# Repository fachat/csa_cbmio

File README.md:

# CBM-IO

Note: this is a part of a larger set of repositories, with [upet_family](https://github.com/fachat/upet_family) as the main repository.

This is the IO board for a re-incarnation of the Commodore PET and B-Series to be used together with the Ultra-CPU board.

It is build on a Eurocard board and has only parts that can still be obtained new in 2025. In fact it uses an FPGA to emulate all the I/O chips of the PET or the B-Series.
It uses the [CS/A bus interface](http://www.6502.org/users/andre/csa/index.html) to connect with the CPU board.

The board at this time can only be programmed as I/O board for the PET, where it includes the original PET I/O (except the 2nd Tape), 
plus the extensions added in the [Ulti-PET](https://github.com/fachat/cbm_ultipet), namely the UART RS232 interfaces and the 2nd
VIA with the IEC bus interface. The VHDL code for this is found in the petio/ folder.

In the future there will be a second option to program the FPGA on the board for the I/O of the B-series.

Note: this is a work in progress!

## Features

## Contributions

### VIA 6522

The VIA6522 is coming from Rhialto's Mega65 code at https://github.com/Rhialto/MegaPET/blob/rhialto/CORE/PET2001_MiSTer/rtl/via6522.vhd
which in turns originates from Gideon Zweijtzer.

I had to adapt it to the single Phi2 clock input though.

In the meantime it has been mostly rewritten esp. in the timer and shift register parts, along the lines
of the chip dissection from http://forum.6502.org .

### UART 16550

The UART seems to be a common 16550 core, made for the Wishbone bus.
it is taken from the Microwatt project https://github.com/antonblanchard/microwatt
and seems to originate from http://www.opencores.org/cores/uart16550/ but that page is not found anymore.

I again had to adapt it to the 6502 bus interface.

## Thanks

Many thanks go to Frank "androSID" Wolf and Dieter "ttlworks" Müller from the
[6502.org forum](https://forum.6502.org), who dissected the PIA and VIA chips (and many more).
This is an outstanding work and absolutely helpful in understanding how the chips work internally.

The relevant chip dissections are

- [VIA dissection](https://6502.org/forum/viewtopic.php?f=4&t=7241)
- [PIA dissection](https://6502.org/forum/viewtopic.php?f=4&t=7425)

For your interest, the full list of chip dissection is here [here on the forum](https://6502.org/forum/viewtopic.php?t=7427)

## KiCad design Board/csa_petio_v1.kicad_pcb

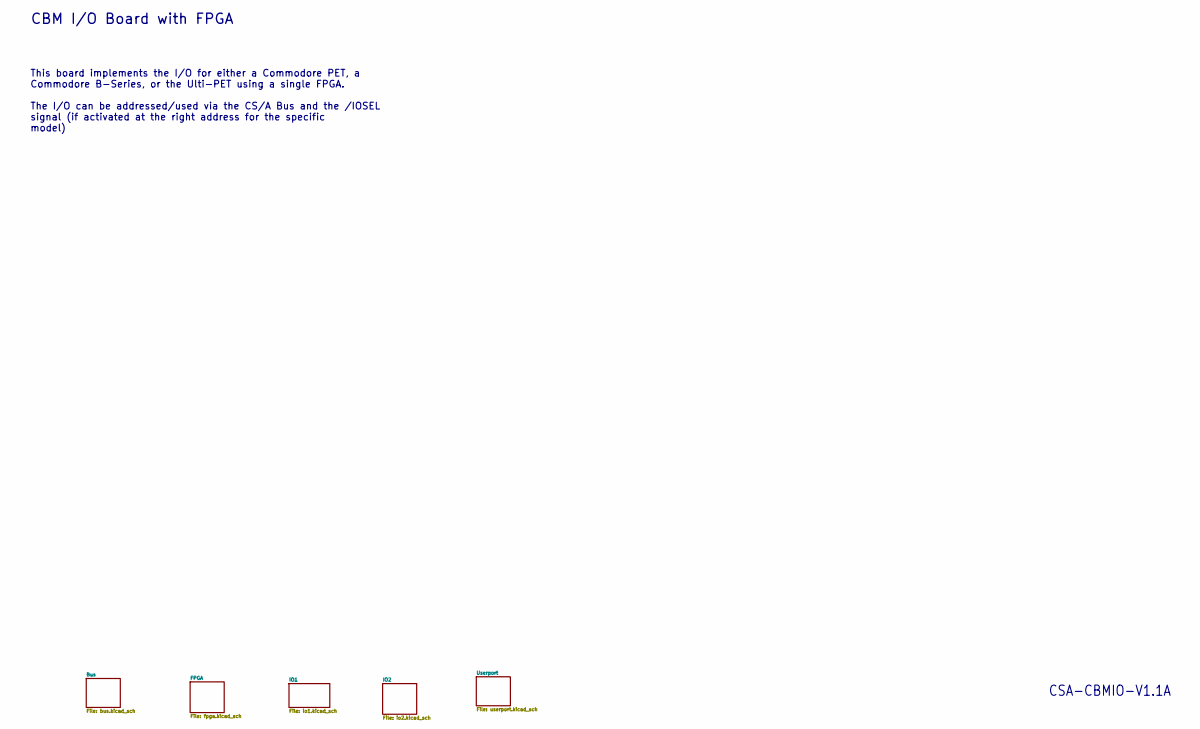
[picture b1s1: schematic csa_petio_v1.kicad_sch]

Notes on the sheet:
CBM I/O Board with FPGA
CSA-CBMIO-V1.1A
This board implements the I/O for either a Commodore PET, a Commodore B-Series, or the Ulti-PET using a single FPGA. The I/O can be addressed/used via the CS/A Bus and the /IOSEL signal (if activated at the right address for the specific model)

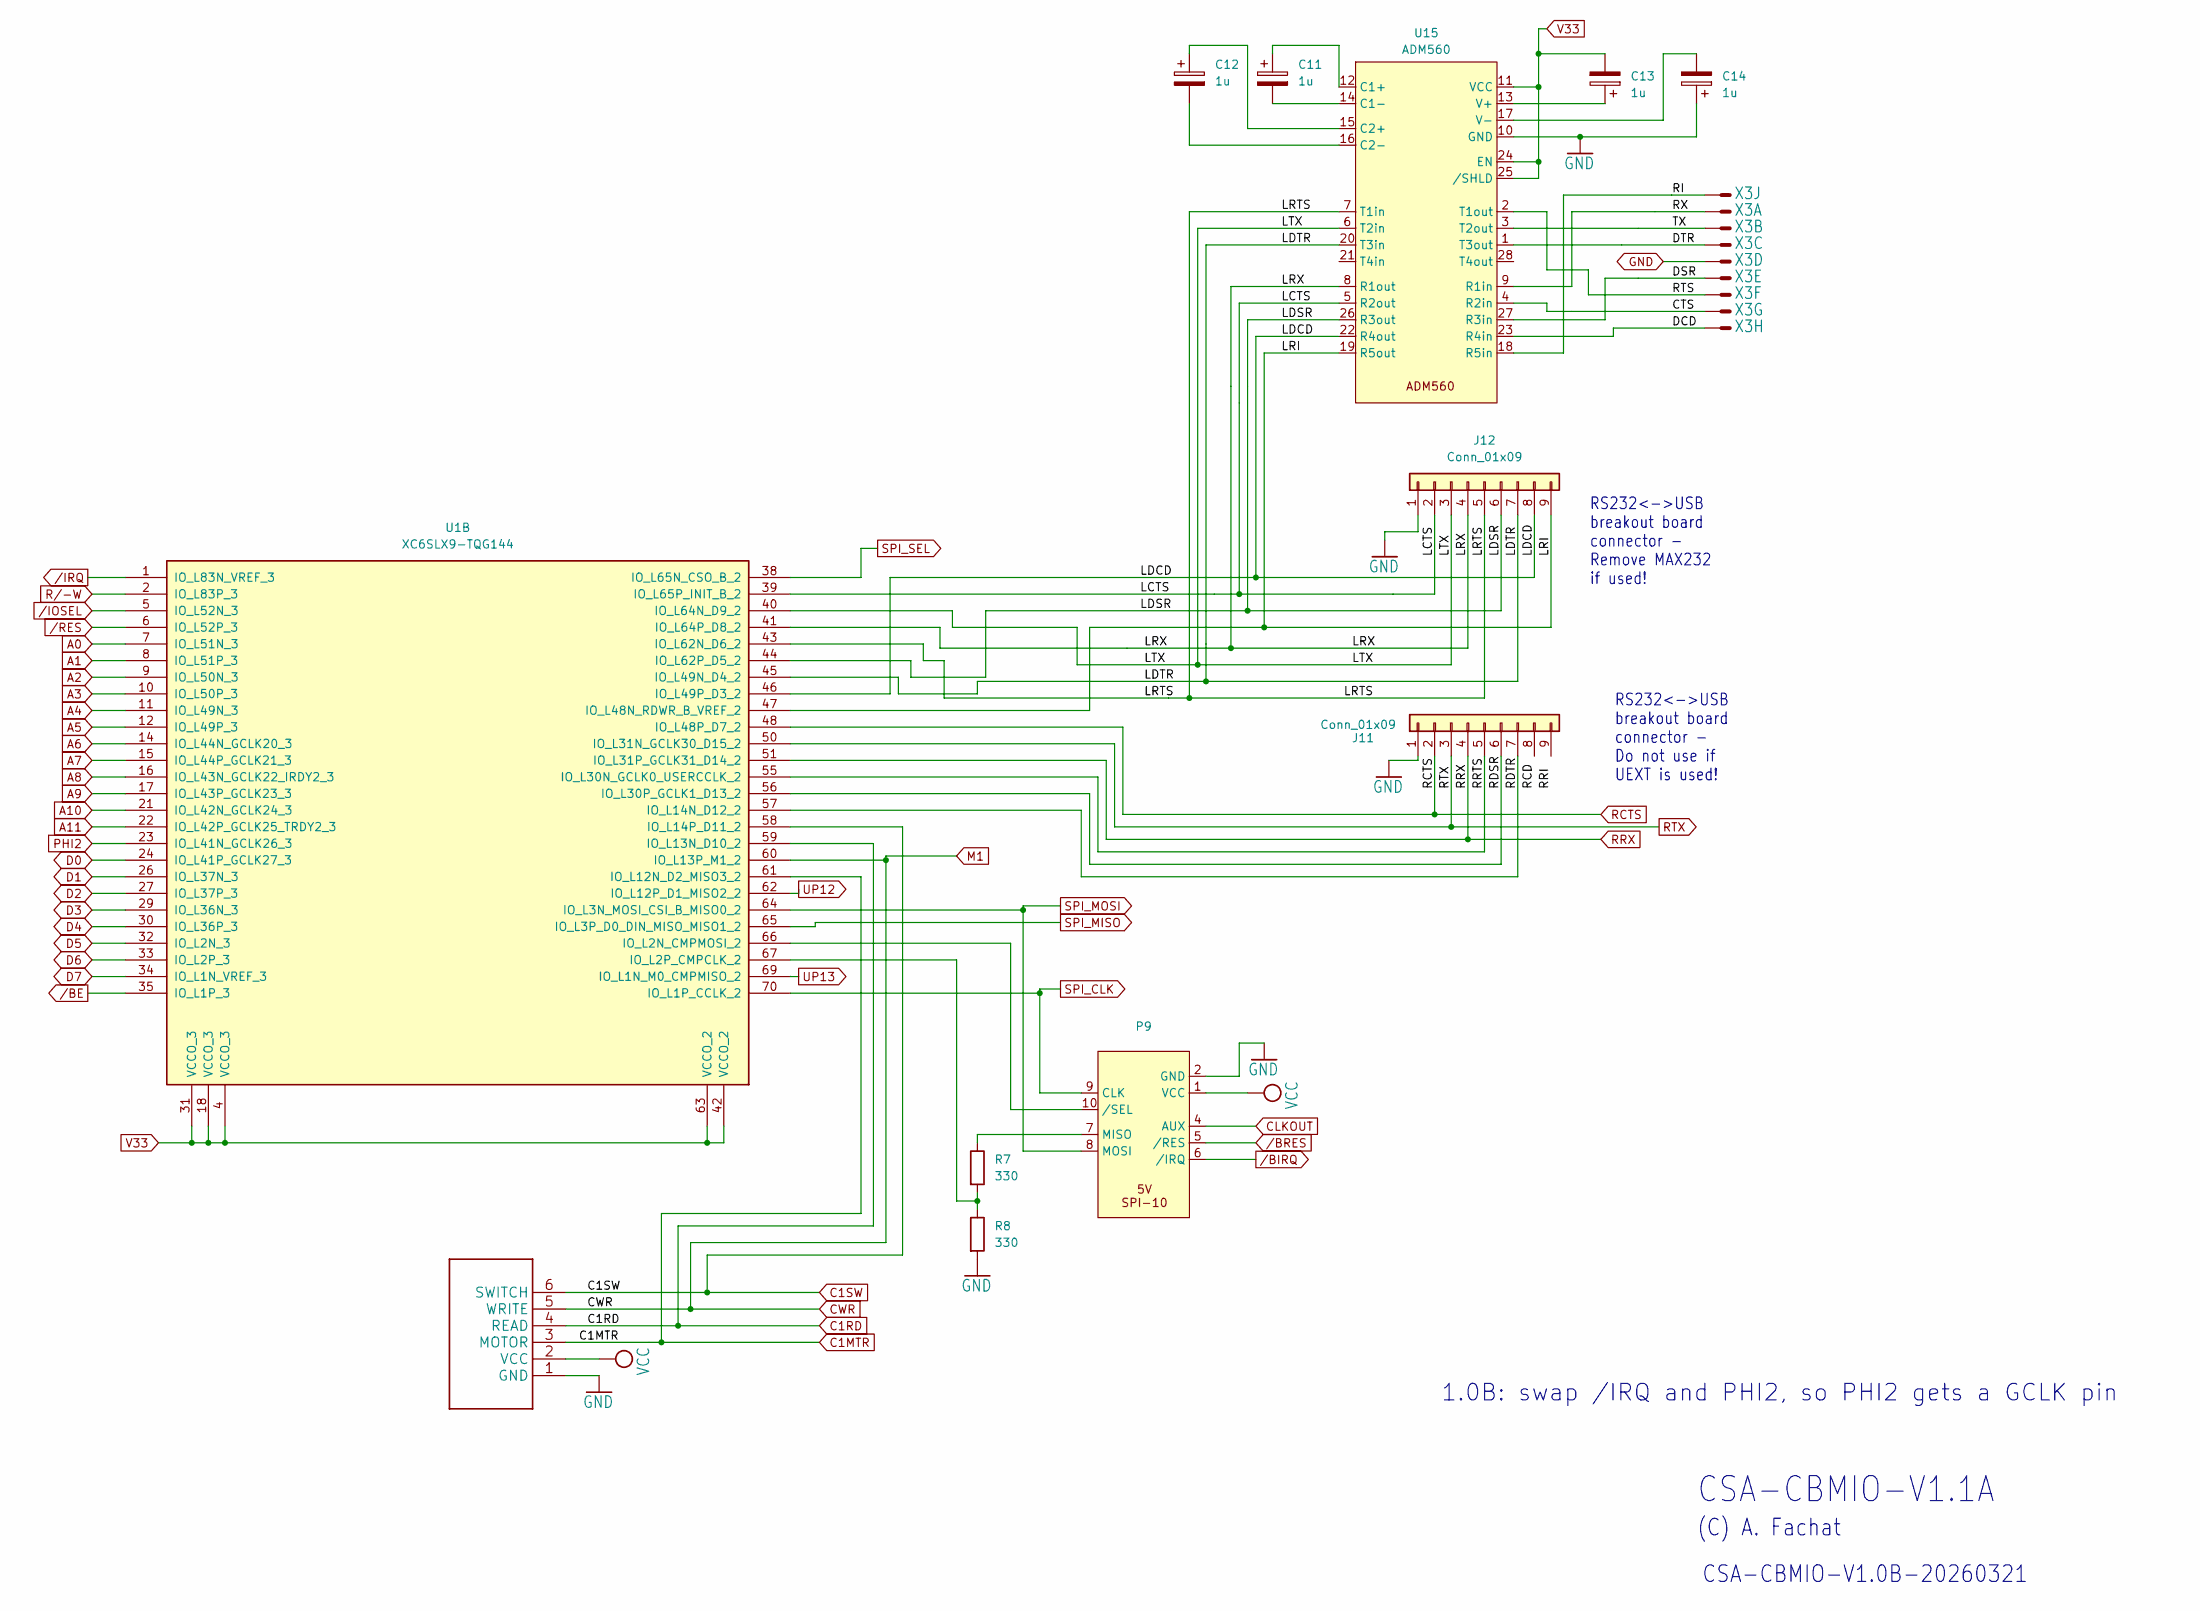
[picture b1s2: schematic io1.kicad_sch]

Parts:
C11, C12, C13, C14: 1u; C_0805_2012Metric_Pad1.18x1.45mm_HandSolder
J11, J12: Conn_01x09; PinHeader_1x09_P2.54mm_Vertical
P5: CBMTAPE; JP6
P9: IDC-Header_2x05_P2.54mm_Vertical
R7, R8: 330; R_0603_1608Metric_Pad0.98x0.95mm_HandSolder
U1: XC6SLX9-TQG144; TQFP-144_20x20mm_P0.5mm
U15: ADM560; SSOP-28_5.3x10.2mm_P0.65mm
X3: M09HPS; DSUB-9_Pins_Horizontal_P2.77x2.84mm_EdgePinOffset9.90mm_Hou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

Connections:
/IO1/CTS: U15.4 (R2in), X3.8 (M)
/IO1/DCD: U15.23 (R4in), X3.9 (M)
/IO1/DSR: U15.27 (R3in), X3.6 (M)
/IO1/DTR: U15.1 (T3out), X3.4 (M)
/IO1/LCTS: J12.2, U1.39 (IO_L65P_INIT_B_2), U15.5 (R2out)
/IO1/LDCD: J12.8, U1.46 (IO_L49P_D3_2), U15.22 (R4out)
/IO1/LDSR: J12.6, U1.44 (IO_L62P_D5_2), U15.26 (R3out)
/IO1/LDTR: J12.7, U1.45 (IO_L49N_D4_2), U15.20 (T3in)
/IO1/LRI: J12.9, U1.47 (IO_L48N_RDWR_B_VREF_2), U15.19 (R5out)
/IO1/LRTS: J12.5, U1.43 (IO_L62N_D6_2), U15.7 (T1in)
/IO1/LRX: J12.4, U1.41 (IO_L64P_D8_2), U15.8 (R1out)
/IO1/LTX: J12.3, U1.40 (IO_L64N_D9_2), U15.6 (T2in)
/IO1/RDSR: J11.6, U1.56 (IO_L30P_GCLK1_D13_2)
/IO1/RDTR: J11.7, U1.57 (IO_L14N_D12_2)
/IO1/RI: U15.18 (R5in), X3.1 (M)
/IO1/RRTS: J11.5, U1.55 (IO_L30N_GCLK0_USERCCLK_2)
/IO1/RTS: U15.2 (T1out), X3.7 (M)
/IO1/RX: U15.9 (R1in), X3.2 (M)
/IO1/TX: U15.3 (T2out), X3.3 (M)
A0: U1.7 (IO_L51N_3); also elsewhere on the board
A1: U1.8 (IO_L51P_3); also elsewhere on the board
A2: U1.9 (IO_L50N_3); also elsewhere on the board
A3: U1.10 (IO_L50P_3); also elsewhere on the board
A4: U1.11 (IO_L49N_3); also elsewhere on the board
A5: U1.12 (IO_L49P_3); also elsewhere on the board
A6: U1.14 (IO_L44N_GCLK20_3); also elsewhere on the board
A7: U1.15 (IO_L44P_GCLK21_3); also elsewhere on the board
A8: U1.16 (IO_L43N_GCLK22_IRDY2_3); also elsewhere on the board
A9: U1.17 (IO_L43P_GCLK23_3); also elsewhere on the board
A10: U1.21 (IO_L42N_GCLK24_3); also elsewhere on the board
A11: U1.22 (IO_L42P_GCLK25_TRDY2_3); also elsewhere on the board
C1MTR: P5.3 (MOTOR), U1.61 (IO_L12N_D2_MISO3_2)
C1RD: P5.4 (READ), U1.59 (IO_L13N_D10_2); also elsewhere on the board
C1SW: P5.6 (SWITCH), U1.58 (IO_L14P_D11_2)
CLKOUT: P9.4 (AUX); also elsewhere on the board
CWR: P5.5 (WRITE), U1.60 (IO_L13P_M1_2); also elsewhere on the board
D0: U1.24 (IO_L41P_GCLK27_3); also elsewhere on the board
D1: U1.26 (IO_L37N_3); also elsewhere on the board
D2: U1.27 (IO_L37P_3); also elsewhere on the board
D3: U1.29 (IO_L36N_3); also elsewhere on the board
D4: U1.30 (IO_L36P_3); also elsewhere on the board
D5: U1.32 (IO_L2N_3); also elsewhere on the board
D6: U1.33 (IO_L2P_3); also elsewhere on the board
D7: U1.34 (IO_L1N_VREF_3); also elsewhere on the board
GND: C14.1, J11.1, J12.1, P5.1 (GND), P9.2 (GND), R8.2, U15.10 (GND), X3.5 (M); also elsewhere on the board
unnamed: P9.7 (MISO), R7.1
unnamed: P9.10 (/SEL), U1.66 (IO_L2N_CMPMOSI_2)
unnamed: R7.2, R8.1, U1.67 (IO_L2P_CMPCLK_2)
unnamed: C11.1, U15.12 (C1+)
unnamed: C11.2, U15.14 (C1-)
unnamed: C12.1, U15.15 (C2+)
unnamed: C12.2, U15.16 (C2-)
unnamed: C13.1, U15.13 (V+)
unnamed: C14.2, U15.17 (V-)
PHI2: U1.23 (IO_L41N_GCLK26_3); also elsewhere on the board
RCTS: J11.2, U1.48 (IO_L48P_D7_2)
RRX: J11.4, U1.51 (IO_L31P_GCLK31_D14_2)
RTX: J11.3, U1.50 (IO_L31N_GCLK30_D15_2)
R/-W: U1.2 (IO_L83P_3); also elsewhere on the board
SPI_CLK: P9.9 (CLK), U1.70 (IO_L1P_CCLK_2); also elsewhere on the board
SPI_MISO: U1.65 (IO_L3P_D0_DIN_MISO_MISO1_2); also elsewhere on the board
SPI_MOSI: P9.8 (MOSI), U1.64 (IO_L3N_MOSI_CSI_B_MISO0_2); also elsewhere on the board
SPI_SEL: U1.38 (IO_L65N_CSO_B_2); also elsewhere on the board
UP12: U1.62 (IO_L12P_D1_MISO2_2); also elsewhere on the board
UP13: U1.69 (IO_L1N_M0_CMPMISO_2); also elsewhere on the board
V33: C13.2, U1.4 (VCCO_3), U1.18 (VCCO_3), U1.31 (VCCO_3), U1.42 (VCCO_2), U1.63 (VCCO_2), U15.11 (VCC), U15.24 (EN), U15.25 (/SHLD); also elsewhere on the board
VCC: P5.2 (VCC), P9.1 (VCC); also elsewhere on the board
/BE: U1.35 (IO_L1P_3); also elsewhere on the board
/BIRQ: P9.6 (/IRQ); also elsewhere on the board
/BRES: P9.5 (/RES); also elsewhere on the board
/IOSEL: U1.5 (IO_L52N_3); also elsewhere on the board
/IRQ: U1.1 (IO_L83N_VREF_3); also elsewhere on the board
/RES: U1.6 (IO_L52P_3); also elsewhere on the board

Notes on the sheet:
1.0B: swap /IRQ and PHI2, so PHI2 gets a GCLK pin
CSA-CBMIO-V1.0B-20260321
RS232<->USB breakout board connector - Do not use if UEXT is used!
RS232<->USB breakout board connector - Remove MAX232 if used!
(C) A. Fachat
CSA-CBMIO-V1.1A

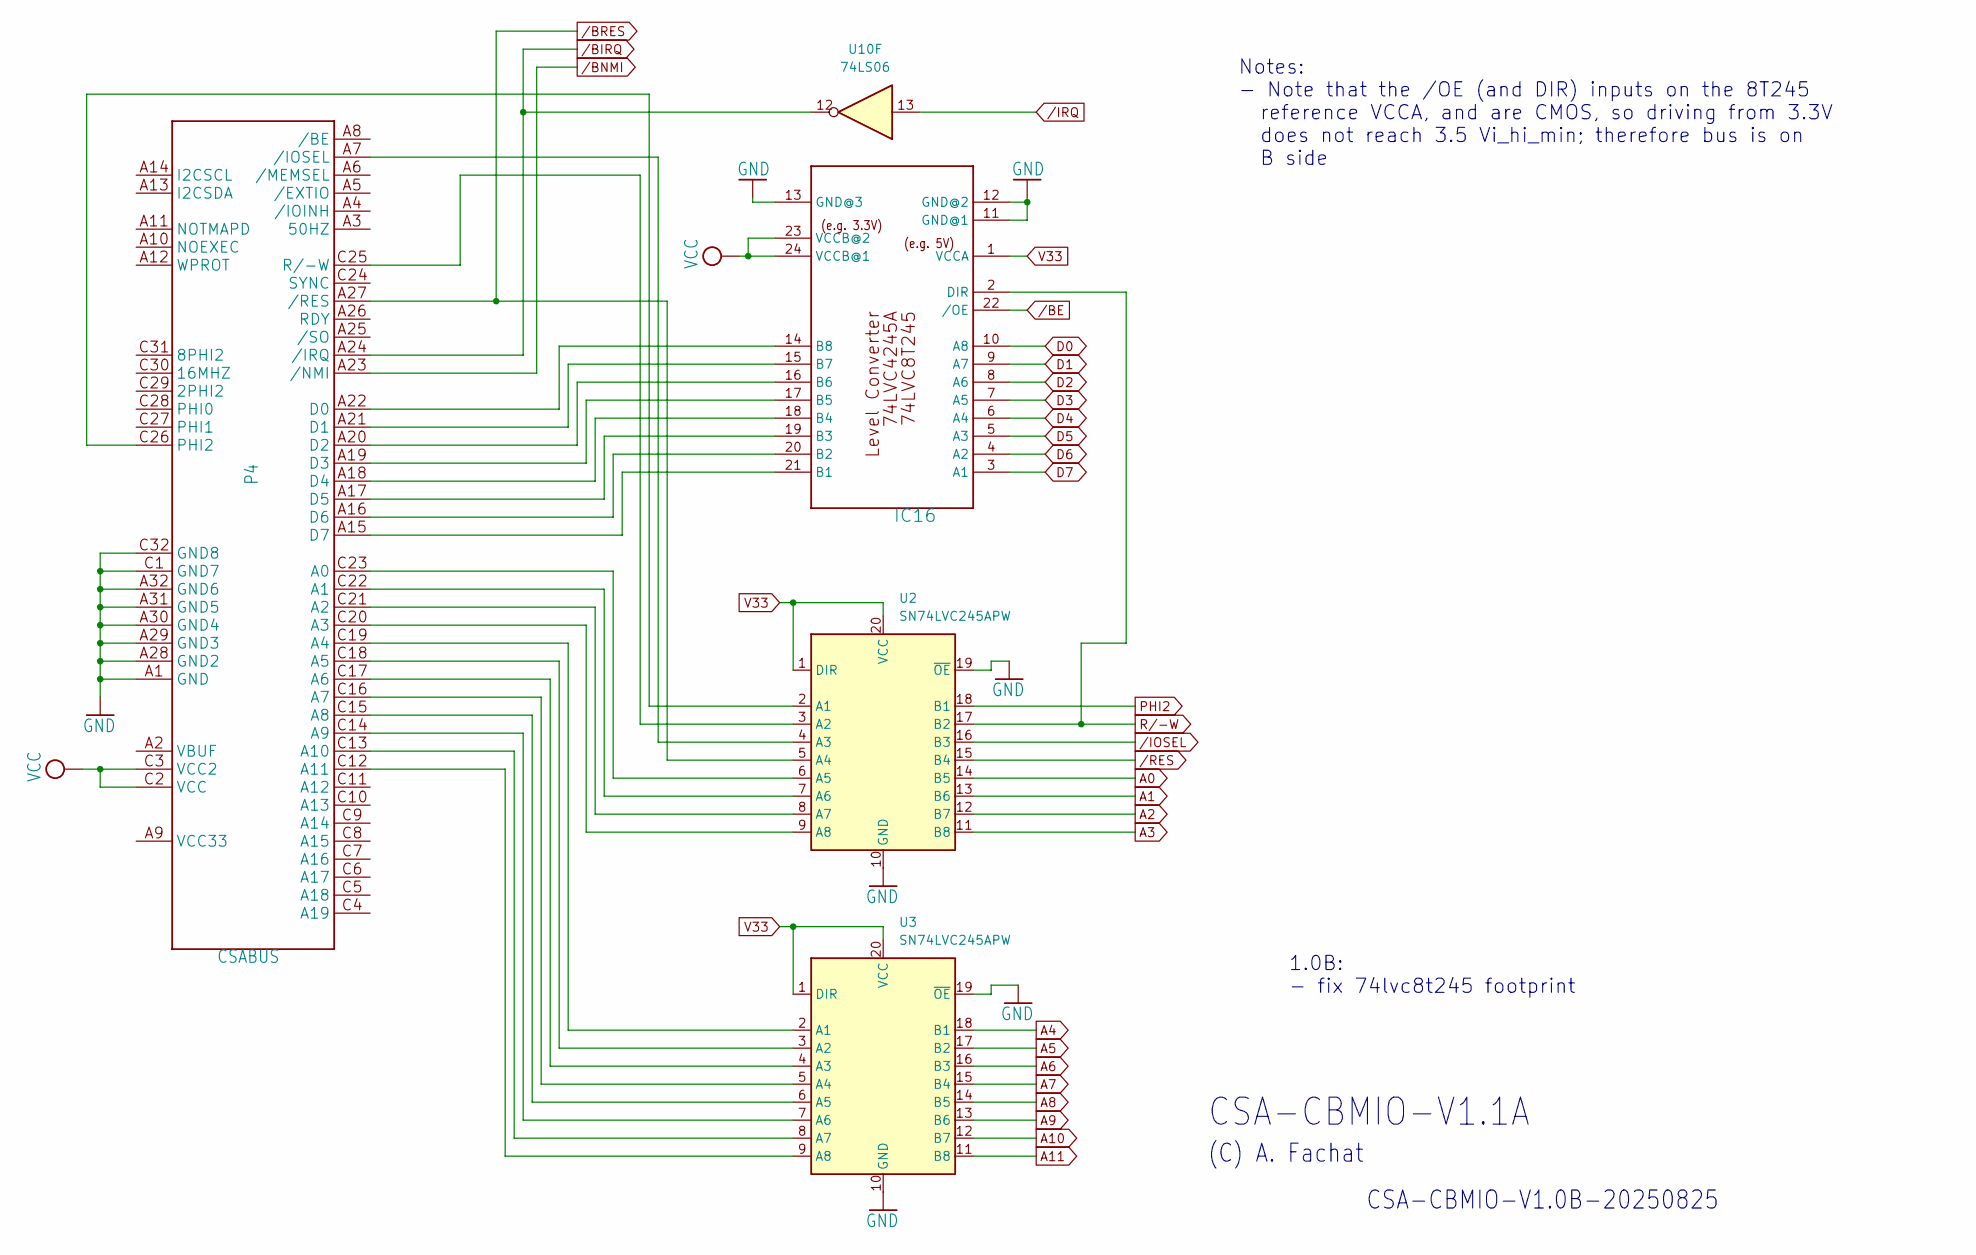
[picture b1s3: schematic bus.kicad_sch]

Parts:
IC16: 74LVC8T245SO24; TSSOP-24_4.4x7.8mm_P0.65mm
P4: CSABUS
U2, U3: SN74LVC245APW; TSSOP-20_4.4x6.5mm_P0.65mm
U10: 74LS06; SO-14_3.9x8.65mm_P1.27mm

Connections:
A0: U2.14 (B5); also elsewhere on the board
A1: U2.13 (B6); also elsewhere on the board
A2: U2.12 (B7); also elsewhere on the board
A3: U2.11 (B8); also elsewhere on the board
A4: U3.18 (B1); also elsewhere on the board
A5: U3.17 (B2); also elsewhere on the board
A6: U3.16 (B3); also elsewhere on the board
A7: U3.15 (B4); also elsewhere on the board
A8: U3.14 (B5); also elsewhere on the board
A9: U3.13 (B6); also elsewhere on the board
A10: U3.12 (B7); also elsewhere on the board
A11: U3.11 (B8); also elsewhere on the board
D0: IC16.10 (A8); also elsewhere on the board
D1: IC16.9 (A7); also elsewhere on the board
D2: IC16.8 (A6); also elsewhere on the board
D3: IC16.7 (A5); also elsewhere on the board
D4: IC16.6 (A4); also elsewhere on the board
D5: IC16.5 (A3); also elsewhere on the board
D6: IC16.4 (A2); also elsewhere on the board
D7: IC16.3 (A1); also elsewhere on the board
GND: IC16.11 (GND@1), IC16.12 (GND@2), IC16.13 (GND@3), P4.A1 (GND), P4.A28 (GND2), P4.A29 (GND3), P4.A30 (GND4), P4.A31 (GND5), P4.A32 (GND6), P4.C1 (GND7), P4.C32 (GND8), U2.10 (GND), U2.19 (~OE), U3.10 (GND), U3.19 (~OE); also elsewhere on the board
unnamed: IC16.21 (B1), P4.A15 (D7)
unnamed: IC16.20 (B2), P4.A16 (D6)
unnamed: IC16.19 (B3), P4.A17 (D5)
unnamed: IC16.18 (B4), P4.A18 (D4)
unnamed: IC16.17 (B5), P4.A19 (D3)
unnamed: IC16.16 (B6), P4.A20 (D2)
unnamed: IC16.15 (B7), P4.A21 (D1)
unnamed: IC16.14 (B8), P4.A22 (D0)
unnamed: P4.C23 (A0), U2.6 (A5)
unnamed: P4.C22 (A1), U2.7 (A6)
unnamed: P4.C21 (A2), U2.8 (A7)
unnamed: P4.C20 (A3), U2.9 (A8)
unnamed: P4.C19 (A4), U3.2 (A1)
unnamed: P4.C18 (A5), U3.3 (A2)
unnamed: P4.C17 (A6), U3.4 (A3)
unnamed: P4.C16 (A7), U3.5 (A4)
unnamed: P4.C15 (A8), U3.6 (A5)
unnamed: P4.C14 (A9), U3.7 (A6)
unnamed: P4.C13 (A10), U3.8 (A7)
unnamed: P4.C12 (A11), U3.9 (A8)
unnamed: P4.C26 (PHI2), U2.2 (A1)
unnamed: P4.C25 (R/-W), U2.3 (A2)
unnamed: P4.A7 (/IOSEL), U2.4 (A3)
PHI2: U2.18 (B1); also elsewhere on the board
R/-W: IC16.2 (DIR), U2.17 (B2); also elsewhere on the board
V33: IC16.1 (VCCA), U2.1 (DIR), U2.20 (VCC), U3.1 (DIR), U3.20 (VCC); also elsewhere on the board
VCC: IC16.23 (VCCB@2), IC16.24 (VCCB@1), P4.C2 (VCC), P4.C3 (VCC2); also elsewhere on the board
/BE: IC16.22 (/OE); also elsewhere on the board
/BIRQ: P4.A24 (/IRQ), U10.12; also elsewhere on the board
/BNMI: P4.A23 (/NMI); also elsewhere on the board
/BRES: P4.A27 (/RES), U2.5 (A4); also elsewhere on the board
/IOSEL: U2.16 (B3); also elsewhere on the board
/IRQ: U10.13; also elsewhere on the board
/RES: U2.15 (B4); also elsewhere on the board

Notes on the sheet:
Notes: - Note that the /OE (and DIR) inputs on the 8T245 reference VCCA, and are CMOS, so driving from 3.3V does not reach 3.5 Vi_hi_min; therefore bus is on B side
CSA-CBMIO-V1.1A
(C) A. Fachat
CSA-CBMIO-V1.0B-20250825
1.0B: - fix 74lvc8t245 footprint

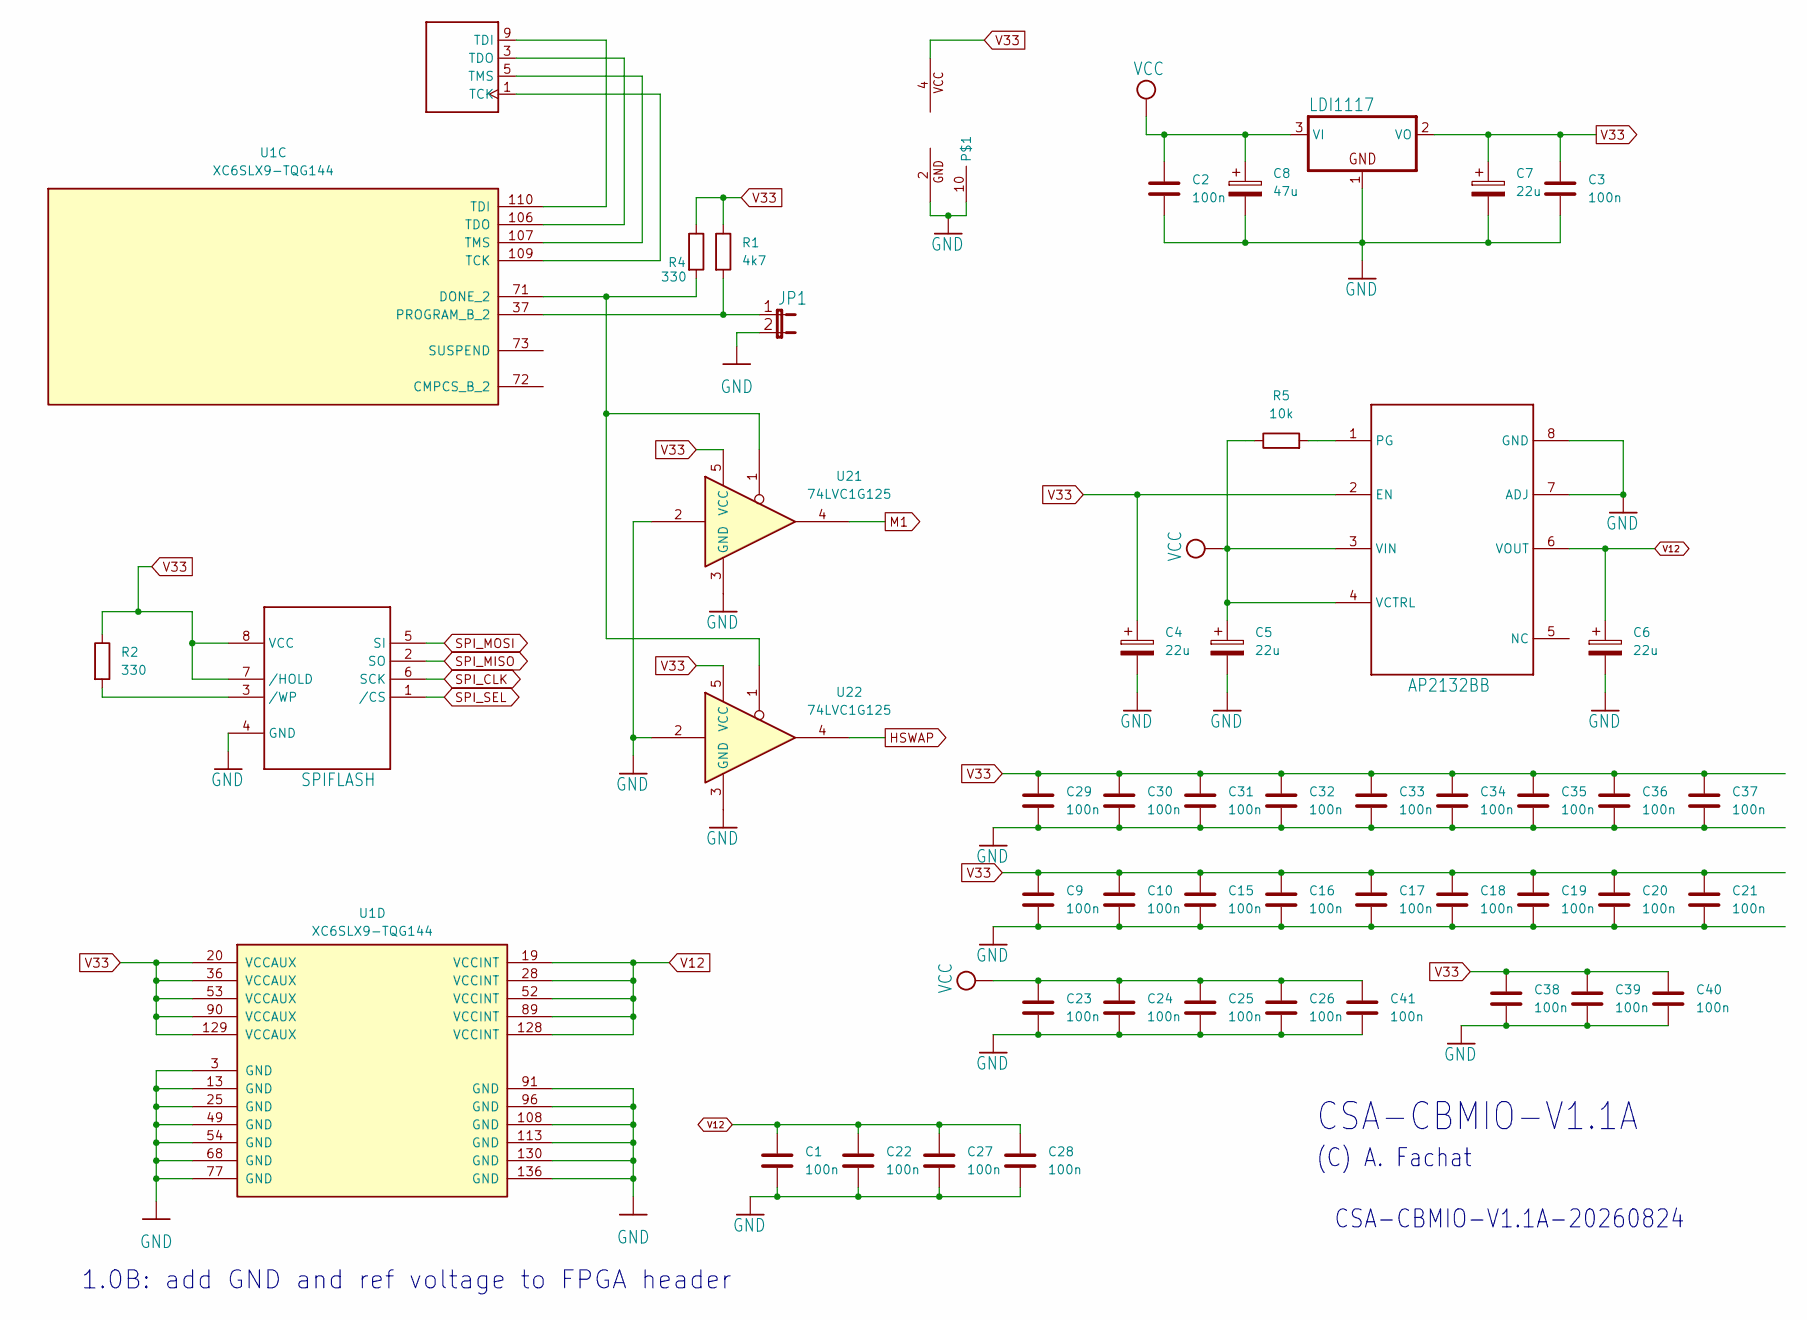
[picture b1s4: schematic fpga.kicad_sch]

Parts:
C1, C2, C3, C9, C10, C15, C16, C17, C18, C19, C20, C21, C22, C23, C24, C25, C26, C27, C28, C29, C30, C31, C32, C33, C34, C35, C36, C37, C38, C39, C40, C41: 100n; C_0805_2012Metric
C4, C5, C6, C7: 22u; C_0805_2012Metric_Pad1.18x1.45mm_HandSolder
C8: 47u; C_0805_2012Metric_Pad1.18x1.45mm_HandSolder
JP1: JP1E; JP1
R1: 4k7; R_0603_1608Metric_Pad0.98x0.95mm_HandSolder
R2, R4: 330; R_0603_1608Metric_Pad0.98x0.95mm_HandSolder
R5: 10k; R_0603_1608Metric_Pad0.98x0.95mm_HandSolder
U1: XC6SLX9-TQG144
U21, U22: 74LVC1G125; SOT-353_SC-70-5
UX7: XILINXPROG; IDC-Header_2x05_P2.54mm_Vertical
UX16: AP2132BB; Diodes_PSOP-8
UX17: LDI1117; SOT-223
UX18: SPIFLASH; DIP-8_W7.62mm_Socket_LongPads

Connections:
CLKOUT: U22.4; also elsewhere on the board
CWR: U21.4; also elsewhere on the board
GND: C1.2, C2.2, C3.2, C4.2, C5.2, C6.2, C7.2, C8.2, C9.2, C10.2, C15.2, C16.2, C17.2, C18.2, C19.2, C20.2, C21.2, C22.2, C23.2, C24.2, C25.2, C26.2, C27.2, C28.2, C29.2, C30.2, C31.2, C32.2, C33.2, C34.2, C35.2, C36.2, C37.2, C38.2, C39.2, C40.2, C41.2, JP1.2, U1.3 (GND), U1.13 (GND), U1.25 (GND), U1.49 (GND), U1.54 (GND), U1.68 (GND), U1.77 (GND), U1.91 (GND), U1.96 (GND), U1.108 (GND), U1.113 (GND), U1.130 (GND), U1.136 (GND), U21.2, U21.3 (GND), U22.2, U22.3 (GND), UX7.2 (GND), UX7.10, UX16.7 (ADJ), UX16.8 (GND), UX17.1 (GND), UX18.4 (GND); also elsewhere on the board
unnamed: R4.2, U1.71 (DONE_2), U21.1, U22.1
unnamed: JP1.1, R1.2, U1.37 (PROGRAM_B_2)
unnamed: U1.109 (TCK), UX7.1 (TCK)
unnamed: U1.110 (TDI), UX7.9 (TDI)
unnamed: U1.106 (TDO), UX7.3 (TDO)
unnamed: U1.107 (TMS), UX7.5 (TMS)
unnamed: R5.2, UX16.1 (PG)
unnamed: R2.2, UX18.3 (/WP)
SPI_CLK: UX18.6 (SCK); also elsewhere on the board
SPI_MISO: UX18.2 (SO); also elsewhere on the board
SPI_MOSI: UX18.5 (SI); also elsewhere on the board
SPI_SEL: UX18.1 (/CS); also elsewhere on the board
V12: C1.1, C6.1, C22.1, C27.1, C28.1, U1.19 (VCCINT), U1.28 (VCCINT), U1.52 (VCCINT), U1.89 (VCCINT), U1.128 (VCCINT), UX16.6 (VOUT)
V33: C3.1, C4.1, C7.1, C9.1, C10.1, C15.1, C16.1, C17.1, C18.1, C19.1, C20.1, C21.1, C29.1, C30.1, C31.1, C32.1, C33.1, C34.1, C35.1, C36.1, C37.1, C38.1, C39.1, C40.1, R1.1, R2.1, R4.1, U1.20 (VCCAUX), U1.36 (VCCAUX), U1.53 (VCCAUX), U1.90 (VCCAUX), U1.129 (VCCAUX), U21.5 (VCC), U22.5 (VCC), UX7.4 (VCC), UX16.2 (EN), UX17.2 (VO), UX18.7 (/HOLD), UX18.8 (VCC); also elsewhere on the board
VCC: C2.1, C5.1, C8.1, C23.1, C24.1, C25.1, C26.1, C41.1, R5.1, UX16.3 (VIN), UX16.4 (VCTRL), UX17.3 (VI); also elsewhere on the board

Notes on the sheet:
CSA-CBMIO-V1.1A
1.0B: add GND and ref voltage to FPGA header
(C) A. Fachat
CSA-CBMIO-V1.1A-20260824
